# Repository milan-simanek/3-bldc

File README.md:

# 3-bldc
3-phase brushless DC motor controller

## Features:
- controls 3-phase BLDC motor
- synchronization using opto-sensors

## Arduino peripherals usage:
- Timer0 - PWM
- Timer1 - generic timer, phase detection
- PB0:5 - phase output
    - PB0: phase 1 - high
    - PB1: phase 2 - high
    - PB2: phase 3 - high
    - PB3: phase 1 - low
    - PB4: phase 2 - low
    - PB5: phase 3 - low
- PC0/PCINT8 - ~FAULT - overcurrent detection
- PC3/ADC3 - output current measurement
- PD0:1 - serial communication
- PD2/INT0 = (zero angle = home position) detection (triggered by both edges)
- PD3/INT1 = step sensor A
- PD4 = step sensor B
- PD5 = OC0B = PWM output

## Issues:
- opto-sensor feedback is currently amplified by operating amplifiers.
  Unfortunately, these devices should operate on higher voltage, so 
  amplification is not so stable and produces flicking.
  Solution: signal from opto-sensors should be amplified and
  conditioned by CMOS invertor based schmitt trigger.

## TODO:
- rotation feedback could be derived from back-EMF.
- maximum speed, acceleration measurements
- use avrm modules for usart communication and text formating (comf)

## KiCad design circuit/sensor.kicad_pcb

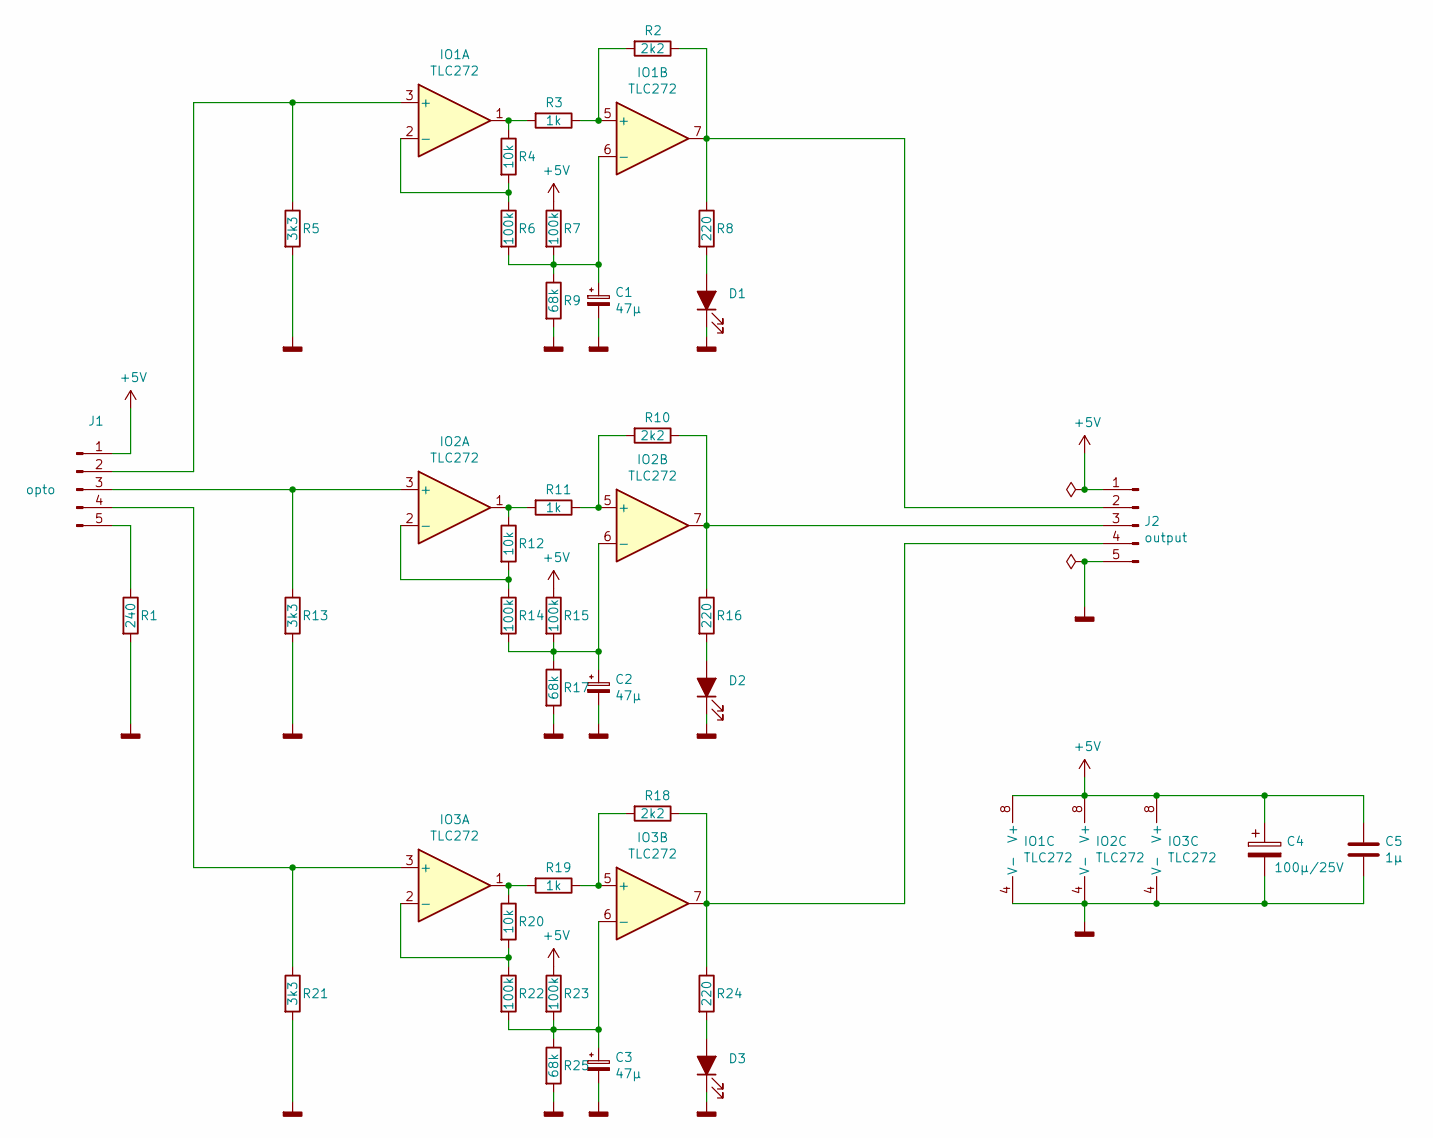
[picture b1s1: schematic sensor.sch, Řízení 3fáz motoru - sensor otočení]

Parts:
C1, C2, C3: 47μ; CP_Radial_D5.0mm_P2.50mm
C4: 100μ/25V; CP_Radial_D6.3mm_P2.50mm
C5: 1μ; C_Rect_L16.5mm_W4.7mm_P15.00mm_MKT
D1, D2, D3: LED_ALT; LED_D3.0mm
IO1, IO2, IO3: TLC272; DIP-8_W7.62mm_LongPads
J1: opto; PinHeader_1x05_P2.54mm_Vertical
J2: output; PinHeader_1x05_P2.54mm_Vertical
R1: 240; R_Axial_DIN0207_L6.3mm_D2.5mm_P10.16mm_Horizontal
R2, R10, R18: 2k2; R_Axial_DIN0207_L6.3mm_D2.5mm_P10.16mm_Horizontal
R3, R11, R19: 1k; R_Axial_DIN0207_L6.3mm_D2.5mm_P10.16mm_Horizontal
R4, R12, R20: 10k; R_Axial_DIN0207_L6.3mm_D2.5mm_P10.16mm_Horizontal
R5, R13, R21: 3k3; R_Axial_DIN0207_L6.3mm_D2.5mm_P10.16mm_Horizontal
R6, R7, R14, R15, R22, R23: 100k; R_Axial_DIN0207_L6.3mm_D2.5mm_P10.16mm_Horizontal
R8, R16, R24: 220; R_Axial_DIN0207_L6.3mm_D2.5mm_P10.16mm_Horizontal
R9, R17, R25: 68k; R_Axial_DIN0207_L6.3mm_D2.5mm_P10.16mm_Horizontal

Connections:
+5V: C4.1, C5.1, IO1.8 (V+), IO2.8 (V+), IO3.8 (V+), J1.1, J2.1, R7.1, R15.1, R23.1
GNDD: C1.2, C2.2, C3.2, C4.2, C5.2, D1.1 (K), D2.1 (K), D3.1 (K), IO1.4 (V-), IO2.4 (V-), IO3.4 (V-), J2.5, R1.2, R5.2, R9.2, R13.2, R17.2, R21.2, R25.2
unnamed: C1.1, IO1.6 (-), R6.2, R7.2, R9.1
unnamed: C2.1, IO2.6 (-), R14.2, R15.2, R17.1
unnamed: C3.1, IO3.6 (-), R22.2, R23.2, R25.1
unnamed: D1.2 (A), R8.2
unnamed: D2.2 (A), R16.2
unnamed: D3.2 (A), R24.2
unnamed: IO1.1, R3.2, R4.1
unnamed: IO1.2 (-), R4.2, R6.1
unnamed: IO1.3 (+), J1.2, R5.1
unnamed: IO1.5 (+), R2.2, R3.1
unnamed: IO1.7, J2.2, R2.1, R8.1
unnamed: IO2.1, R11.2, R12.1
unnamed: IO2.2 (-), R12.2, R14.1
unnamed: IO2.3 (+), J1.3, R13.1
unnamed: IO2.5 (+), R10.2, R11.1
unnamed: IO2.7, J2.3, R10.1, R16.1
unnamed: IO3.1, R19.2, R20.1
unnamed: IO3.2 (-), R20.2, R22.1
unnamed: IO3.3 (+), J1.4, R21.1
unnamed: IO3.5 (+), R18.2, R19.1
unnamed: IO3.7, J2.4, R18.1, R24.1
unnamed: J1.5, R1.1

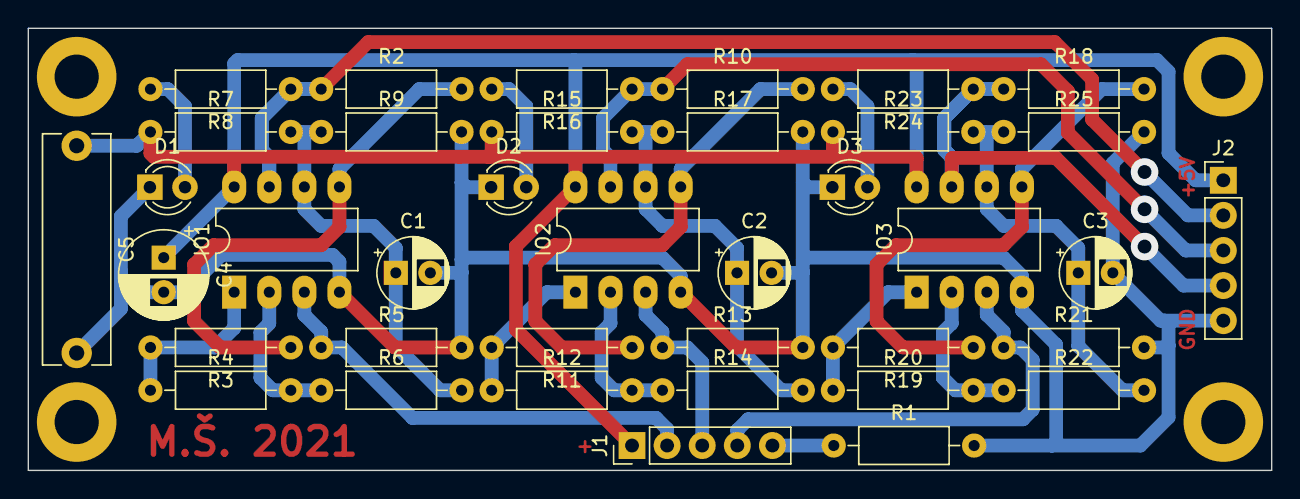
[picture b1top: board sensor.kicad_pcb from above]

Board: 2 copper layers, 90.0 x 32.0 mm, 38 parts (0 on the bottom side), 24 nets.

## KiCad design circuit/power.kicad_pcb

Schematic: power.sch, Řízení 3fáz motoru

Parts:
C1: 15n; C_Rect_L4.6mm_W2.0mm_P2.50mm_MKS02_FKP02
C2, C4, C9: 330n; C213_L16_W7.5_P12.5
C3: 22μ; CP_Axial_L18.0mm_D6.5mm_P25.00mm_Horizontal
C5, C6, C7: 4μ7; CP_Radial_Tantal_D4.5mm_P2.50mm
C8: 1000μ/16V; CP_Radial_D10.0mm_P5.00mm
D1: error; LED_D5.0mm
D2, D3, D4, D5, D6, D7, D8, D9, D10: 1N4937; D_DO-41_SOD81_P10.16mm_Horizontal
IO1: CD4071; DIP-14_W7.62mm_LongPads
IO2: IR2130; DIP-28_W15.24mm_LongPads
J1: control; PinHeader_1x12_P2.54mm_Vertical
J2: test; PinHeader_1x06_P2.54mm_Vertical
J3: test; PinHeader_1x05_P2.54mm_Vertical
J4: power; BarrelJack_Horizontal
J5: power12; PinHeader_1x02_P2.54mm_Vertical
J6: motor; PinHeader_1x04_P2.54mm_Vertical
J7: msensor; PinHeader_1x04_P2.54mm_Vertical
P1: 680; Potentiometer_ACP_CA9-H5_Horizontal
P2: 220; Potentiometer_ACP_CA9-H5_Horizontal
R1, R2: 15k; R_Axial_DIN0207_L6.3mm_D2.5mm_P10.16mm_Horizontal
R3: 100k; R_Axial_DIN0207_L6.3mm_D2.5mm_P10.16mm_Horizontal
R4, R8: 1k; R_Axial_DIN0207_L6.3mm_D2.5mm_P10.16mm_Horizontal
R5: 10k; R_Axial_DIN0207_L6.3mm_D2.5mm_P10.16mm_Horizontal
R6: 0.5Ω/5W; R_Axial_Power_L25.0mm_W9.0mm_P30.48mm
R7: 220; R_Axial_DIN0207_L6.3mm_D2.5mm_P10.16mm_Horizontal
R9: 100; R_Axial_DIN0207_L6.3mm_D2.5mm_P10.16mm_Horizontal
R10, R11, R12, R13, R14, R15: 18; R_Axial_DIN0207_L6.3mm_D2.5mm_P10.16mm_Horizontal
T1: BSS83P; SOT-23
T2, T3, T4, T5, T6, T7: BUZ11; TO-220-3_Vertical
TL1: STOP; Tlacitko_hranate

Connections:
+5V: C2.1, C3.1, IO1.14, J1.2, R5.2, T1.3, TL1.2, TL1.3, TL1.5, TL1.6
+12V: C4.1, C8.1, C9.1, D5.1, D7.1, D9.1, IO2.1, J1.1, J4.1, J5.2, R9.1, T2.2, T4.2, T6.2
/CAO: IO2.10, J1.11, J3.3, R2.2, R3.2
/GNDPWR: C9.2, D6.2, D8.2, D10.2, IO2.13, R6.2, R8.1, T3.3, T5.3, T7.3
/L1: C5.2, D5.2, D6.1, IO2.26, J6.2, J7.2, T2.3, T3.2
/L2: C6.2, D7.2, D8.1, IO2.22, J6.3, J7.3, T4.3, T5.2
/L3: C7.2, D9.2, D10.1, IO2.18, J6.4, J7.4, T6.3, T7.2
/stop: C1.1, IO1.8, R1.2, TL1.1, TL1.4
/~FAULT: IO2.8, J1.10, J3.1, R5.1, T1.1
GNDD: C1.2, C2.2, C3.2, C4.2, C8.2, IO1.7, IO2.12, J1.12, J3.5, J4.2, J5.1, P1.3, P2.1, R1.1, R4.1, R6.1, R7.1
unnamed: C5.1, D2.1, IO2.28
unnamed: C6.1, D3.1, IO2.24
unnamed: C7.1, D4.1, IO2.20
unnamed: D1.1 (K), R7.2
unnamed: D1.2 (A), T1.2
unnamed: D2.2, D3.2, D4.2, R9.2
unnamed: IO1.1, J1.5
unnamed: IO1.3, IO2.3, J2.2
unnamed: IO1.4, IO2.4, J2.3
unnamed: IO1.6, J1.6
unnamed: IO1.9, J1.3
unnamed: IO1.2, IO1.5, IO1.10, IO1.12
unnamed: IO1.11, IO2.2, J2.1
unnamed: IO1.13, J1.4
unnamed: IO2.5, J1.7, J2.4
unnamed: IO2.6, J1.8, J2.5
unnamed: IO2.7, J1.9, J2.6
unnamed: IO2.9, J3.2, P2.2
unnamed: IO2.11, J3.4, P1.2, R3.1, R4.2
unnamed: IO2.14, R15.2
unnamed: IO2.15, R14.2
unnamed: IO2.16, R13.2
unnamed: IO2.19, R12.2
unnamed: IO2.23, R11.2
unnamed: IO2.27, R10.2
unnamed: J6.1, J7.1
unnamed: P1.1, R2.1
unnamed: P2.3, R8.2
unnamed: R10.1, T2.1
unnamed: R11.1, T4.1
unnamed: R12.1, T6.1
unnamed: R13.1, T3.1
unnamed: R14.1, T5.1
unnamed: R15.1, T7.1

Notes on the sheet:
12V DC

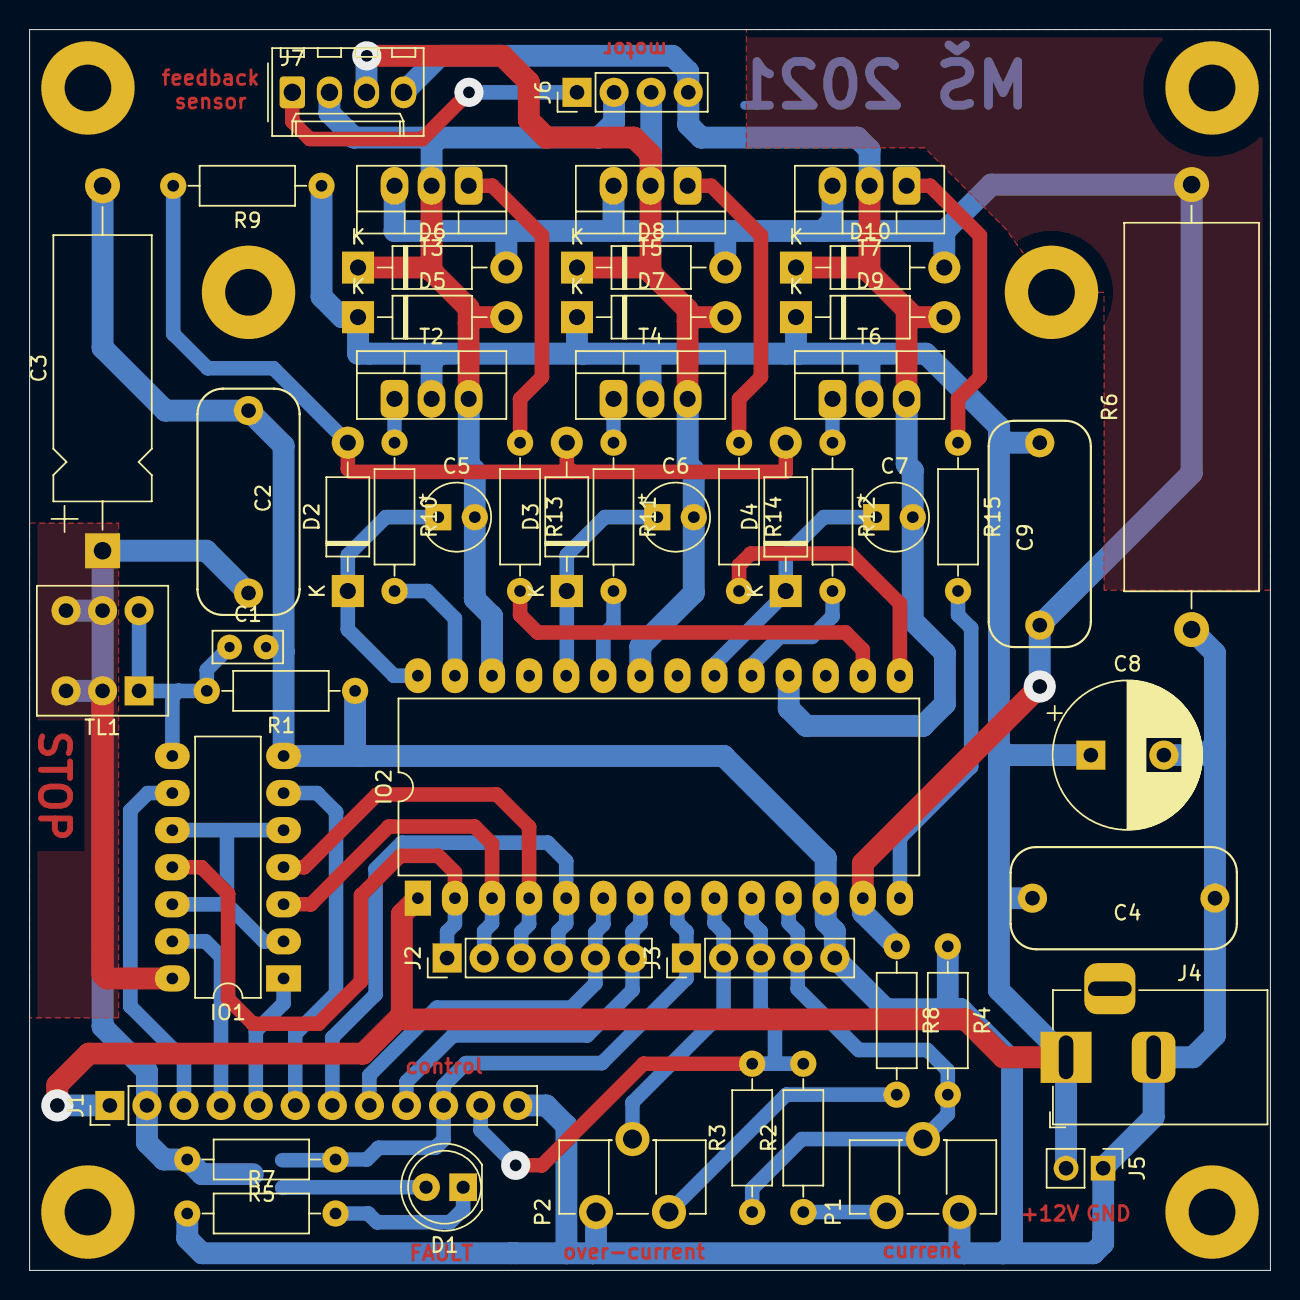
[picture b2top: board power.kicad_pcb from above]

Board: 2 copper layers, 85.0 x 85.0 mm, 53 parts (1 on the bottom side), 44 nets.

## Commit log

2022-02-15 initial implementation
2022-02-16 move to standard usart+comf modules
2022-02-16 add module: ledkey
2022-02-16 add schematics
2022-02-16 add .gitignore
